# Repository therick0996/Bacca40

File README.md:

# Bacca40

## FAQ:
#### Why tho? 
Don't let your memes be dreams

#### Does it have split spacebar?
No

#### Does it have backlighting?
No

#### Does it have RGB?
No

#### Does it have a rotary encoder?
No

#### Does it have hotswap?
No

#### Does it have Alps support?
No

#### Choc support?
No

#### Will you add any of these?
No

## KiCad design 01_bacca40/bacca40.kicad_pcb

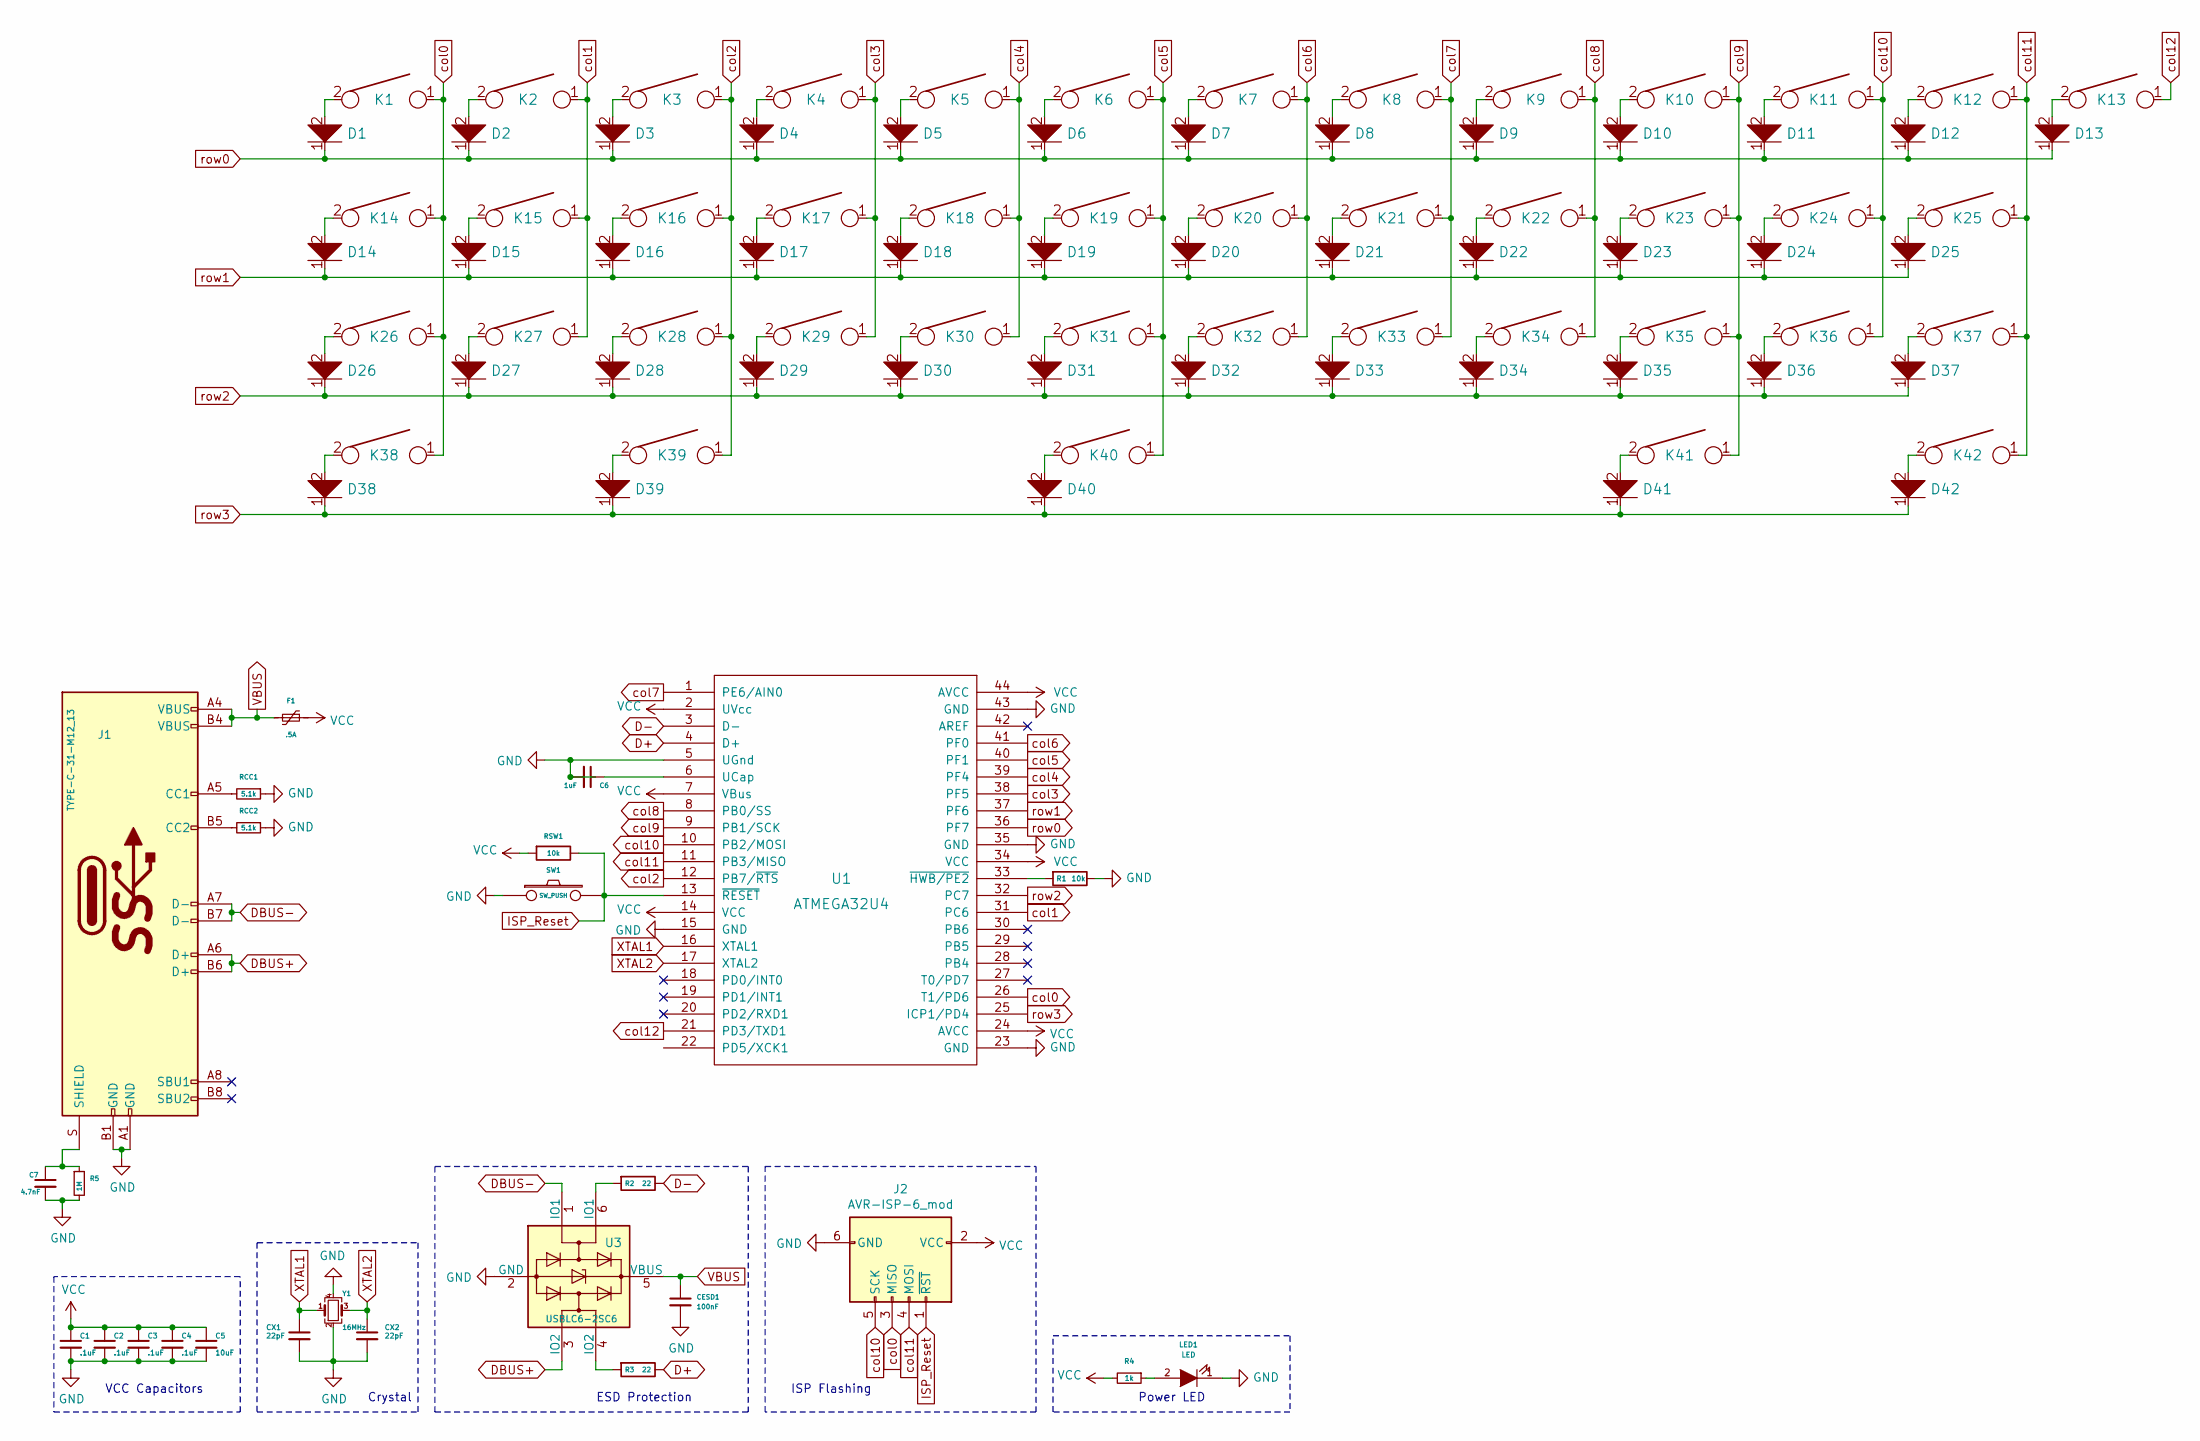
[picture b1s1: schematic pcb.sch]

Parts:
C1, C2, C3, C4: .1uF; C_0805_2012Metric_Pad1.15x1.40mm_HandSolder
C5: 10uF; C_0805_2012Metric_Pad1.15x1.40mm_HandSolder
C6: 1uF; C_0805_2012Metric_Pad1.15x1.40mm_HandSolder
C7: 4.7nF; C_0805_2012Metric_Pad1.15x1.40mm_HandSolder
CESD1: 100nF; C_0805_2012Metric_Pad1.15x1.40mm_HandSolder
CX1, CX2: 22pF; C_0805_2012Metric_Pad1.15x1.40mm_HandSolder
D1, D2, D3, D4, D5, D6, D7, D8, D9, D10, D11, D12, D13, D14, D15, D16, D17, D18, D19, D20, D21, D22, D23, D24, D25, D26, D27, D28, D29, D30, D31, D32, D33, D34, D35, D36, D37, D38, D39, D40, D41, D42: D; D_SOD-123_modified
F1: .5A; Fuse_0805_2012Metric_Pad1.15x1.40mm_HandSolder
J1: TYPE-C-31-M12_13; TYPE-C-31-M-12
J2: AVR-ISP-6_mod; PIN_HEADER_1x6_OFFSET
K1, K2, K3, K4, K5, K6, K7, K8, K9, K10, K11, K12, K13, K15, K16, K17, K18, K19, K20, K21, K22, K23, K24, K27, K28, K29, K30, K31, K32, K33, K34, K35, K37: KEYSW; MX_PCB_100H
K14, K36, K38, K39, K41, K42: KEYSW; MX_PCB_125H
K25, K26: KEYSW; MX_PCB_175H
K40: KEYSW; MX_PCB_625H
LED1: LED; LED_0805_2012Metric_Pad1.15x1.40mm_HandSolder
R1: 10k; R_0805_2012Metric_Pad1.15x1.40mm_HandSolder
R2, R3: 22; R_0805_2012Metric_Pad1.15x1.40mm_HandSolder
R4: 1k; R_0805_2012Metric_Pad1.15x1.40mm_HandSolder
R5: 1M; R_0805_2012Metric_Pad1.15x1.40mm_HandSolder
RCC1, RCC2: 5.1k; R_0805_2012Metric_Pad1.15x1.40mm_HandSolder
RSW1: 10k; R_0805_2012Metric_Pad1.15x1.40mm_HandSolder
SW1: SW_PUSH; SKQG-1155865
U1: ATMEGA32U4; ATMEGA32U4-AU
U3: USBLC6-2SC6; SOT-23-6
Y1: 16MHz; Crystal_SMD_3225-4Pin_3.2x2.5mm_HandSoldering

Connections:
D+: R3.1, U1.4 (D+)
D-: R2.1, U1.3 (D-)
DBUS+: J1.A6 (D+), J1.B6 (D+), U3.3 (IO2)
DBUS-: J1.A7 (D-), J1.B7 (D-), U3.1 (IO1)
GND: C1.2, C2.2, C3.2, C4.2, C5.2, C6.2, C7.2, CESD1.2, CX1.2, CX2.2, J1.A1 (GND), J1.B1 (GND), J2.6 (GND), LED1.1 (K), R1.1, R5.2, RCC1.1, RCC2.1, SW1.1, U1.5 (UGnd), U1.15 (GND), U1.23 (GND), U1.35 (GND), U1.43 (GND), U3.2 (GND), Y1.2, Y1.4
ISP_Reset: J2.1 (~RST), RSW1.1, SW1.2, U1.13 (~RESET)
unnamed: C6.1, U1.6 (UCap)
unnamed: C7.1, J1.S (SHIELD), R5.1
unnamed: D1.2, K1.2
unnamed: D2.2, K2.2
unnamed: D3.2, K3.2
unnamed: D4.2, K4.2
unnamed: D5.2, K5.2
unnamed: D6.2, K6.2
unnamed: D7.2, K7.2
unnamed: D8.2, K8.2
unnamed: D9.2, K9.2
unnamed: D10.2, K10.2
unnamed: D11.2, K11.2
unnamed: D12.2, K12.2
unnamed: D13.2, K13.2
unnamed: D14.2, K14.2
unnamed: D15.2, K15.2
unnamed: D16.2, K16.2
unnamed: D17.2, K17.2
unnamed: D18.2, K18.2
unnamed: D19.2, K19.2
unnamed: D20.2, K20.2
unnamed: D21.2, K21.2
unnamed: D22.2, K22.2
unnamed: D23.2, K23.2
unnamed: D24.2, K24.2
unnamed: D25.2, K25.2
unnamed: D26.2, K26.2
unnamed: D27.2, K27.2
unnamed: D28.2, K28.2
unnamed: D29.2, K29.2
unnamed: D30.2, K30.2
unnamed: D31.2, K31.2
unnamed: D32.2, K32.2
unnamed: D33.2, K33.2
unnamed: D34.2, K34.2
unnamed: D35.2, K35.2
unnamed: D36.2, K36.2
unnamed: D37.2, K37.2
unnamed: D38.2, K38.2
unnamed: D39.2, K39.2
unnamed: D40.2, K40.2
unnamed: D41.2, K41.2
unnamed: D42.2, K42.2
unnamed: J1.A5 (CC1), RCC1.2
unnamed: J1.B5 (CC2), RCC2.2
unnamed: LED1.2 (A), R4.1
unnamed: R1.2, U1.33 (~HWB/PE2)
unnamed: R2.2, U3.6 (IO1)
unnamed: R3.2, U3.4 (IO2)
VBUS: CESD1.1, F1.2, J1.A4 (VBUS), J1.B4 (VBUS), U3.5 (VBUS)
VCC: C1.1, C2.1, C3.1, C4.1, C5.1, F1.1, J2.2 (VCC), R4.2, RSW1.2, U1.2 (UVcc), U1.7 (VBus), U1.14 (VCC), U1.24 (AVCC), U1.34 (VCC), U1.44 (AVCC)
XTAL1: CX1.1, U1.16 (XTAL1), Y1.1
XTAL2: CX2.1, U1.17 (XTAL2), Y1.3
col0: J2.3 (MISO), K1.1, K14.1, K26.1, K38.1, U1.26 (T1/PD6)
col1: K2.1, K15.1, K27.1, U1.31 (PC6)
col2: K3.1, K16.1, K28.1, K39.1, U1.12 (PB7/~RTS)
col3: K4.1, K17.1, K29.1, U1.38 (PF5)
col4: K5.1, K18.1, K30.1, U1.39 (PF4)
col5: K6.1, K19.1, K31.1, K40.1, U1.40 (PF1)
col6: K7.1, K20.1, K32.1, U1.41 (PF0)
col7: K8.1, K21.1, K33.1, U1.1 (PE6/AIN0)
col8: K9.1, K22.1, K34.1, U1.8 (PB0/SS)
col9: K10.1, K23.1, K35.1, K41.1, U1.9 (PB1/SCK)
col10: J2.5 (SCK), K11.1, K24.1, K36.1, U1.10 (PB2/MOSI)
col11: J2.4 (MOSI), K12.1, K25.1, K37.1, K42.1, U1.11 (PB3/MISO)
col12: K13.1, U1.21 (PD3/TXD1)
row0: D1.1, D2.1, D3.1, D4.1, D5.1, D6.1, D7.1, D8.1, D9.1, D10.1, D11.1, D12.1, D13.1, U1.36 (PF7)
row1: D14.1, D15.1, D16.1, D17.1, D18.1, D19.1, D20.1, D21.1, D22.1, D23.1, D24.1, D25.1, U1.37 (PF6)
row2: D26.1, D27.1, D28.1, D29.1, D30.1, D31.1, D32.1, D33.1, D34.1, D35.1, D36.1, D37.1, U1.32 (PC7)
row3: D38.1, D39.1, D40.1, D41.1, D42.1, U1.25 (ICP1/PD4)

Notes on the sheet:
ESD Protection
Crystal
VCC Capacitors
Power LED
ISP Flashing

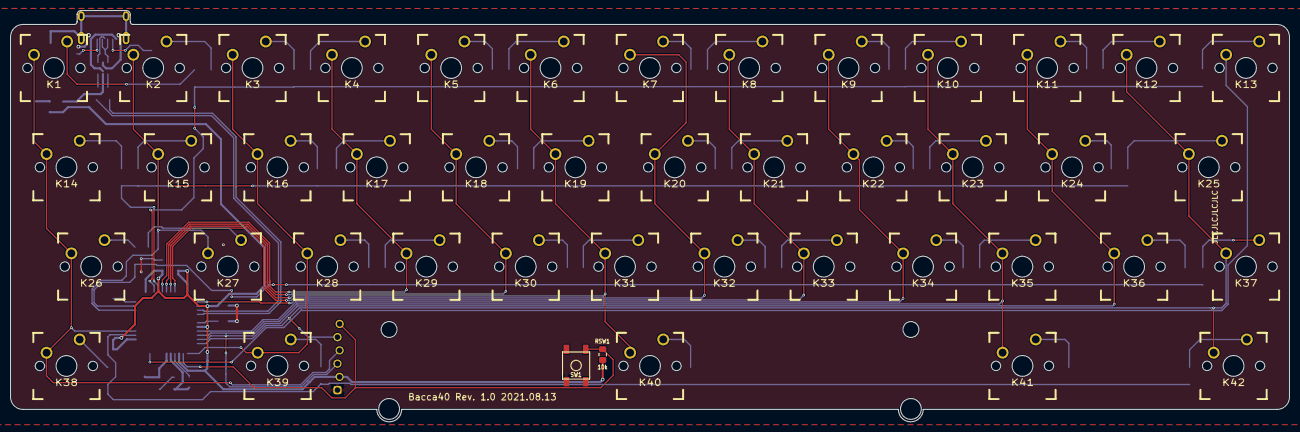
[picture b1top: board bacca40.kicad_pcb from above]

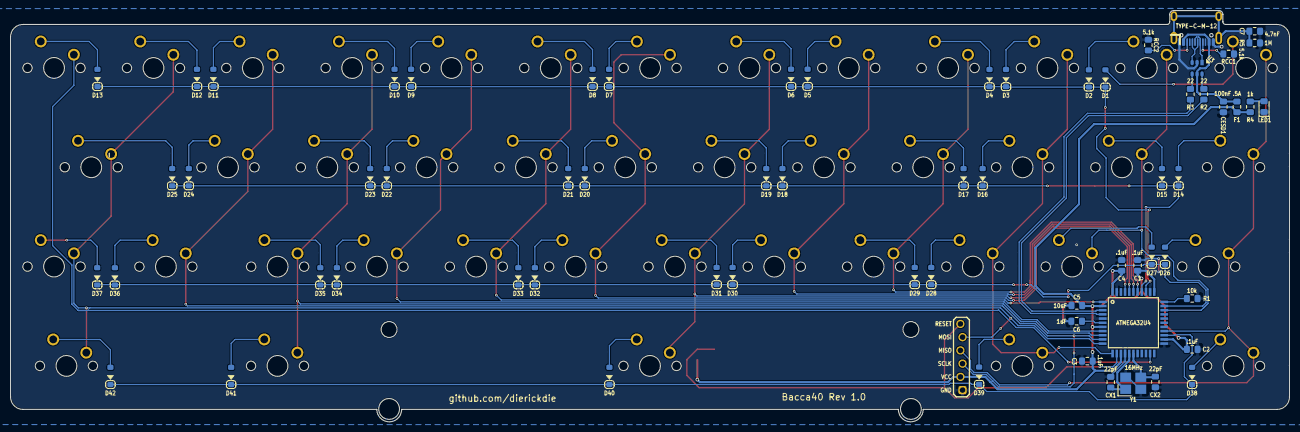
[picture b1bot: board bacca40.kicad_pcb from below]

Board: 2 copper layers, 245.3 x 78.9 mm, 110 parts (66 on the bottom side), 77 nets.

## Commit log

2021-08-13 Initial commit
    placed footprints
2021-08-13 USB/MCU routed
2021-08-14 Fully routed?
2021-08-14 Removed Ori stuff
2021-08-14 add fr4 plate
2021-08-14 update plate
2021-10-17 rename files
2022-03-28 add .gitignore
2022-04-27 gitignore
